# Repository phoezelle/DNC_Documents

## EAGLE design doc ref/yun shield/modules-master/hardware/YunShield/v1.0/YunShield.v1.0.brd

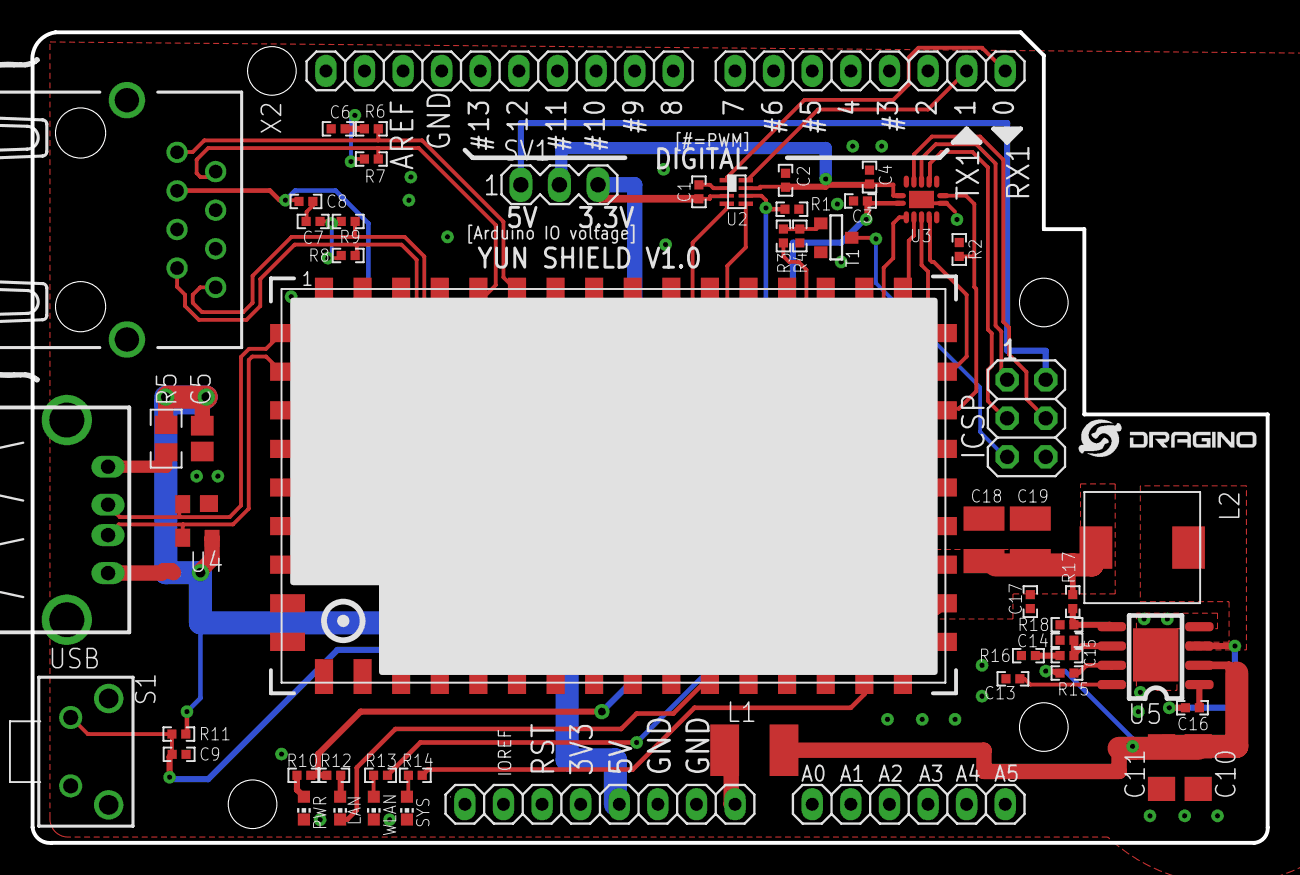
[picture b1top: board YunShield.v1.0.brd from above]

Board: 2 copper layers, 81.3 x 53.3 mm, 58 parts (0 on the bottom side), 48 nets.

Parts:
C1, C2, C3, C4: 0.1uF; C0402
C5: 10uF, 10V; C0805
C6, C7, C8: 0.1u 10v; C0402
C9: 0.1u NL; C0402
C10: 10uF 25V; C1206
C11: 10uF 25v NL; C1206
C13: 0.1u 10V; C0402
C14, C17: NL; C0402
C15: 3900pF 25V; C0402
C16: 0.01uF 16V; C0402
C18, C19: 22uF; C1210
ICSP: ICSP; 2X03
J2, J3: 8x1F-H8.5; 1X08
J4: 6x1F-H8.5; 1X06
JP1: 10x1F-H8.5; 1X10
L1: 500ma; L1812
L2: 10uH; INDUCTOR-74
LAN: Yellow; CHIP-LED0603
PWR: Yellow; CHIP-LED0603
R1, R2: 10k; R0402
R3, R4: 47k; R0402
R5: PTC; R0805
R6, R7, R8, R9: 49.9R; R0402
R10, R12: 330R; R0402
R11, R15: 100K; R0402
R13, R14: 270R; R0402
R16: 6.81K; R0402
R17: 26.1K; R0402
R18: 10K; R0402
S1: SWITCH_6X6X5
SV1: MA03-1
SYS: Yellow; CHIP-LED0603
T1: AP2302GN-HF/SOT23; SOT-23
U1: HE; HE50
U2: NTB0102GT; NXP-SOT833-1
U3: NTB0104; DHVQFN14
U4: YSSR05; SOT143
U5: RT8250; RT8250-SOP8
U$1: LOGO-NEW; LOGO-SILK-NEW
USB: PN87520
WLAN: Yellow; CHIP-LED0603
X2: RJ111BE

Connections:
2.5V: C3.2, U1.36, U3.1
+3V3: C1.2, C17.1, C18.1, C19.1, L2.P$2, R10.1, R12.1, R17.2, SV1.3, U1.23, U1.24, U2.3
+5V: C5.1, ICSP.2, J3.5, R5.1, R11.2, SV1.1, U4.4
/RESET: ICSP.5, T1.1
CTRL_2.0V: C8.1, U1.2, X2.3
GND: C1.1, C2.1, C3.1, C4.1, C5.2, C6.2, C7.2, C8.2, C9.2, C10.1, C11.1, C13.2, C14.2, C17.2, C18.2, C19.2, ICSP.6, J3.6, J3.7, JP1.7, PWR.C, R1.1, R2.1, R4.2, R16.1, R18.1, S1.2, S1.3, S1.4, SYS.C, T1.2, U1.1, U1.4, U1.7, U1.10, U1.13, U1.22, U1.25, U1.26, U1.32, U1.35, U1.40, U1.42, U1.44, U1.45, U1.48, U2.2, U3.7, U3.EXP, U4.1, U5.4, U5.9, USB.4, WLAN.C
GPIO18: U1.18, U3.5
GPIO19: R2.2, U1.19, U3.8
GPIO20: R3.2, U1.20
GPIO21: U1.16, U3.3
GPIO22: U1.17, U3.4
GPIO23: U1.21, U3.2
GPIO24: R1.2, U1.3, U2.6
GPIO28: R14.1, U1.27
JUMPSTART: C9.1, R11.1, S1.1, U1.37
LED_P0: LAN.C, U1.31
LED_WLAN: R13.1, U1.30
MISO: ICSP.1, U3.11
MOSI: ICSP.4, U3.12
unnamed: R3.1, R4.1, T1.3
unnamed: R5.2, USB.1
unnamed: C6.1, R6.1, R7.1
unnamed: PWR.A, R10.2
unnamed: C7.1, R8.1, R9.1
unnamed: LAN.A, R12.2
unnamed: R13.2, WLAN.A
unnamed: R14.2, SYS.A
unnamed: C10.2, C11.2, L1.2, R15.2, U5.2
unnamed: R15.1, U5.7
unnamed: R17.1, R18.2, U5.5
unnamed: C13.1, U5.8
unnamed: C14.1, C15.1, U5.6
unnamed: C15.2, R16.2
unnamed: C16.1, U5.1
unnamed: C16.2, L2.P$1, U5.3
P0_RX_N: R9.2, U1.8, X2.8
P0_RX_P: R8.2, U1.9, X2.7
P0_TX_N: R7.2, U1.5, X2.2
P0_TX_P: R6.2, U1.6, X2.1
RX: J2.1, U2.1
SCK: ICSP.3, U3.10
TX: J2.2, U2.8
UART_RX: U1.33, U2.5
UART_TX: U1.34, U2.4
USB_N: U1.50, U4.2, USB.2
USB_P: U1.49, U4.3, USB.3
VDC: C2.2, C4.2, SV1.2, U2.7, U3.14
VIN: J3.8, L1.1

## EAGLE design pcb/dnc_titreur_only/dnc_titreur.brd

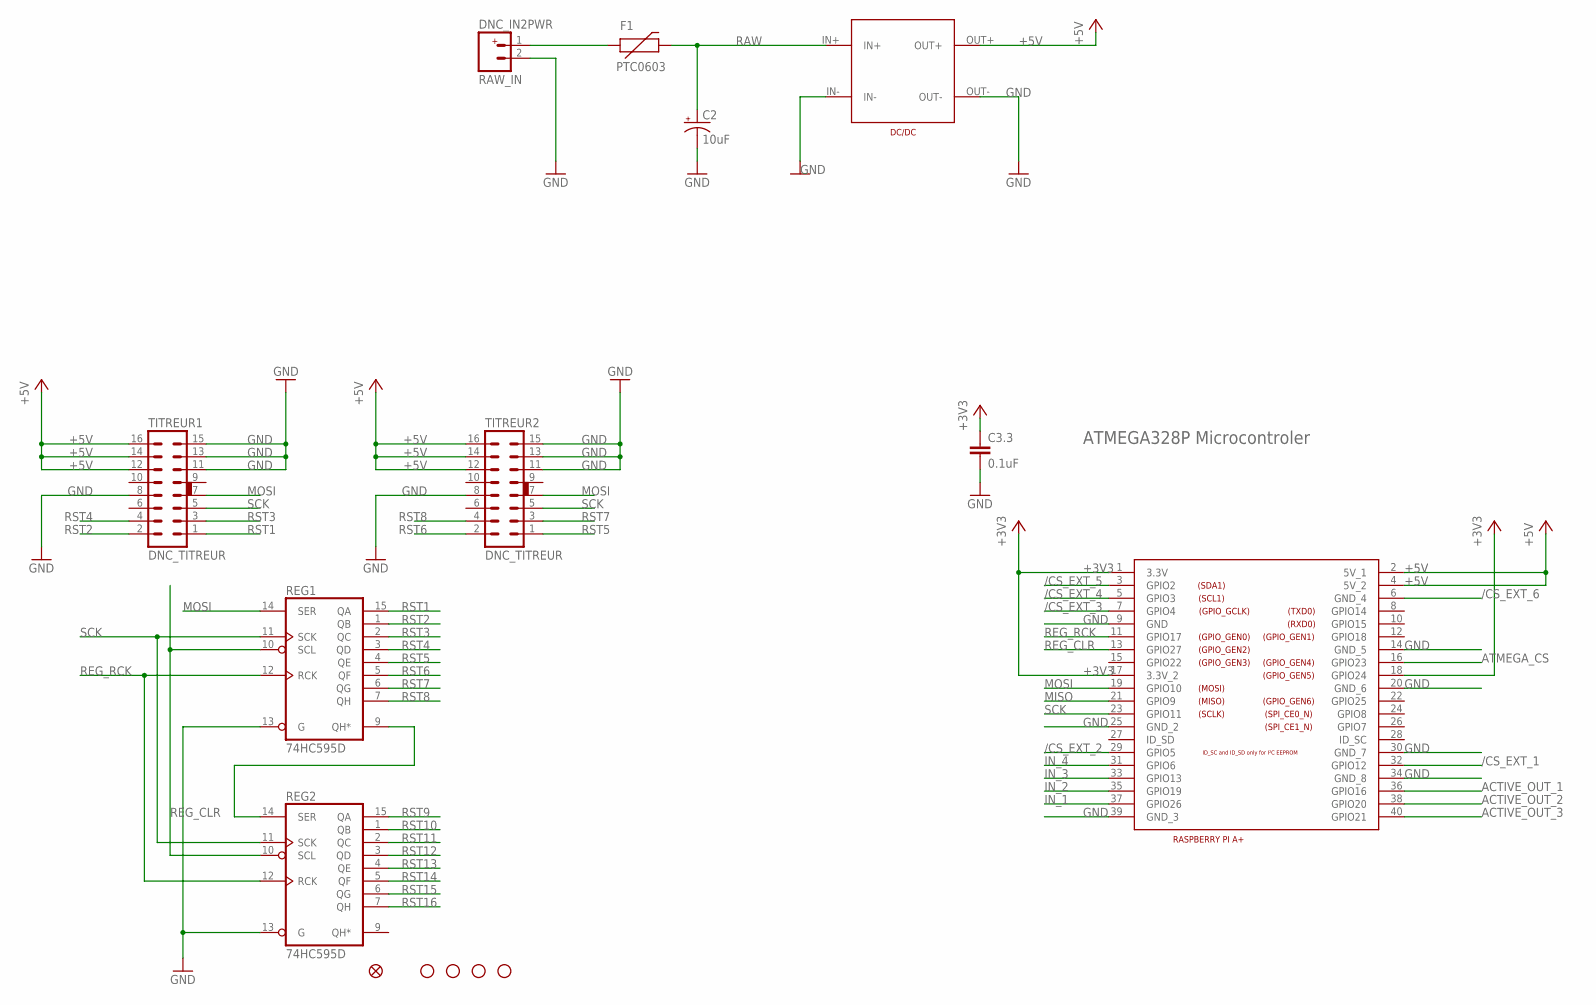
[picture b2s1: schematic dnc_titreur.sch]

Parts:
C2: 10uF; EIA3216
C3.3: 0.1uF; C0805
F1: PTC0603; 0603
JP14: FIDUCIAL1X2.5; FIDUCIAL-1X2.5
JP15, JP16, JP17, JP18: STAND-OFF
RAW_IN: DNC_IN2PWR; DNC_IN2_PWR
REG1, REG2: 74HC595D; SO16
TITREUR1, TITREUR2: DNC_TITREUR
U$4: RASPIA+
U$5: DC/DC_SEED

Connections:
+3V3: C3.3.1, U$4.1 (3.3V), U$4.17 (3.3V_2), U$4.18 (GPIO24)
+5V: TITREUR1.12, TITREUR1.14, TITREUR1.16, TITREUR2.12, TITREUR2.14, TITREUR2.16, U$4.2 (5V_1), U$4.4 (5V_2), U$5.OUT+
/CS_EXT_1: U$4.32 (GPIO12)
/CS_EXT_2: U$4.29 (GPIO5)
/CS_EXT_3: U$4.7 (GPIO4)
/CS_EXT_4: U$4.5 (GPIO3)
/CS_EXT_5: U$4.3 (GPIO2)
/CS_EXT_6: U$4.6 (GND_4)
ACTIVE_OUT_1: U$4.36 (GPIO16)
ACTIVE_OUT_2: U$4.38 (GPIO20)
ACTIVE_OUT_3: U$4.40 (GPIO21)
ATMEGA_CS: U$4.16 (GPIO23)
GND: C2.C (-), C3.3.2, RAW_IN.2, REG1.8 (GND), REG1.13 (G), REG2.8 (GND), REG2.13 (G), TITREUR1.8, TITREUR1.11, TITREUR1.13, TITREUR1.15, TITREUR2.8, TITREUR2.11, TITREUR2.13, TITREUR2.15, U$4.9 (GND), U$4.14 (GND_5), U$4.20 (GND_6), U$4.25 (GND_2), U$4.30 (GND_7), U$4.34 (GND_8), U$4.39 (GND_3), U$5.IN-, U$5.OUT-
IN_1: U$4.37 (GPIO26)
IN_2: U$4.35 (GPIO19)
IN_3: U$4.33 (GPIO13)
IN_4: U$4.31 (GPIO6)
MISO: U$4.21 (GPIO9)
MOSI: REG1.14 (SER), TITREUR1.7, TITREUR2.7, U$4.19 (GPIO10)
unnamed: REG1.9 (QH*), REG2.14 (SER)
unnamed: F1.1, RAW_IN.1
RAW: C2.A (+), F1.2, U$5.IN+
REG_CLR: REG1.10 (SCL), REG2.10 (SCL), U$4.13 (GPIO27)
REG_RCK: REG1.12 (RCK), REG2.12 (RCK), U$4.11 (GPIO17)
RST1: REG1.15 (QA), TITREUR1.1
RST2: REG1.1 (QB), TITREUR1.2
RST3: REG1.2 (QC), TITREUR1.3
RST4: REG1.3 (QD), TITREUR1.4
RST5: REG1.4 (QE), TITREUR2.1
RST6: REG1.5 (QF), TITREUR2.2
RST7: REG1.6 (QG), TITREUR2.3
RST8: REG1.7 (QH), TITREUR2.4
RST9: REG2.15 (QA)
RST10: REG2.1 (QB)
RST11: REG2.2 (QC)
RST12: REG2.3 (QD)
RST13: REG2.4 (QE)
RST14: REG2.5 (QF)
RST15: REG2.6 (QG)
RST16: REG2.7 (QH)
SCK: REG1.11 (SCK), REG2.11 (SCK), TITREUR1.5, TITREUR2.5, U$4.23 (GPIO11)
VCC: REG1.16 (VCC), REG2.16 (VCC)

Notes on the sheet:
ATMEGA328P Microcontroler

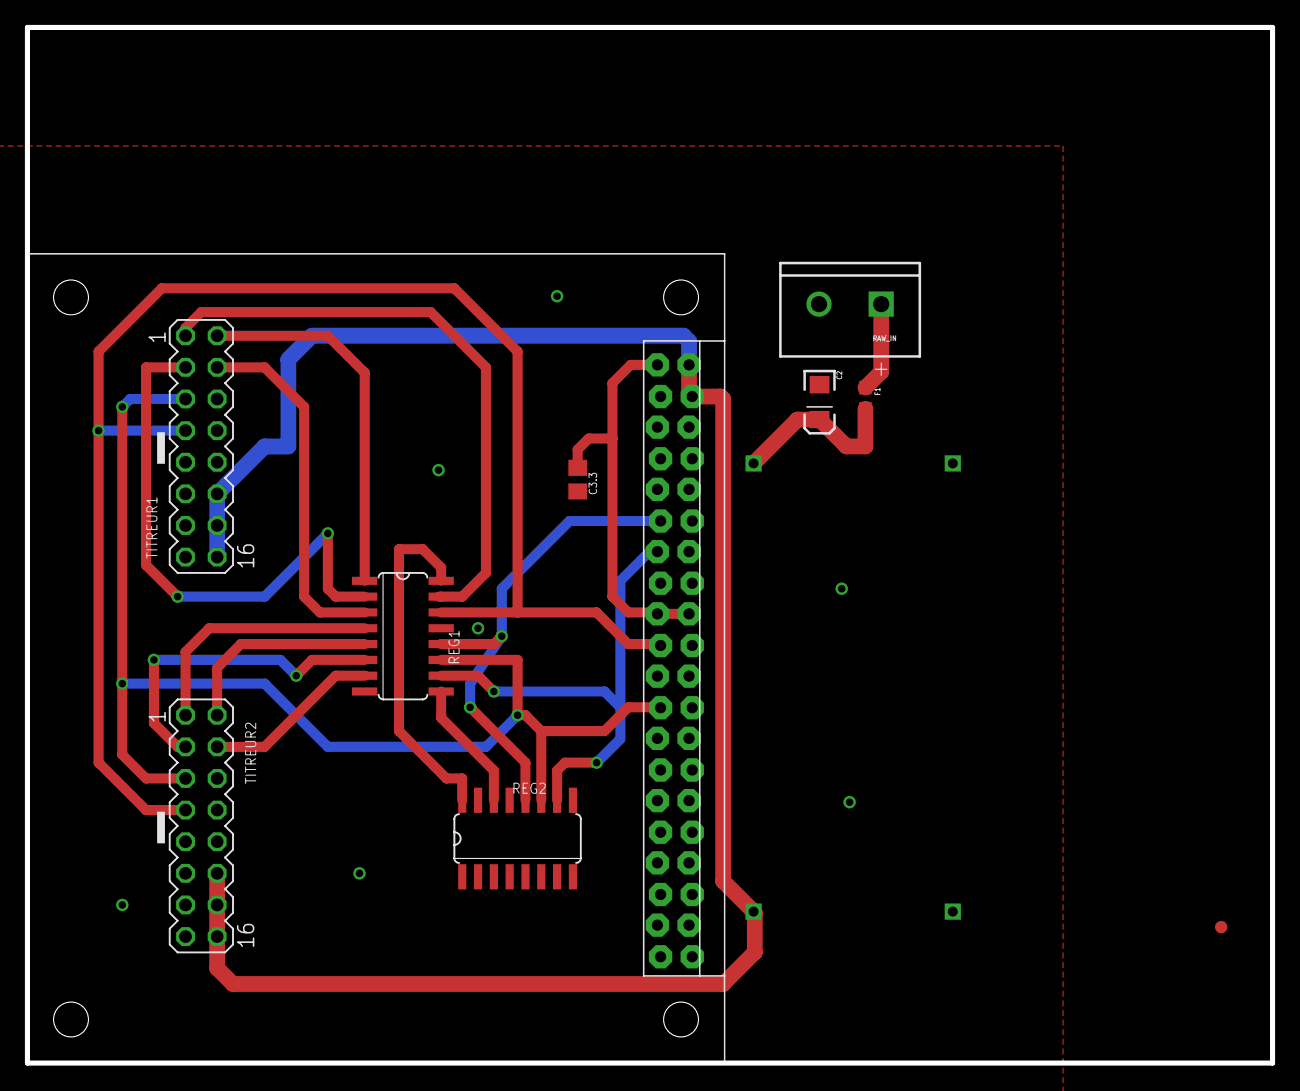
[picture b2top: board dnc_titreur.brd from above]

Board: 2 copper layers, 100.0 x 83.2 mm, 15 parts (0 on the bottom side), 19 nets.

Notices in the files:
parts and their libraries:
SparkFun: Licensing: CC v3.0 Share-Alike You are welcome to use this library for commercial purposes.
SparkFun-PowerIC: Licensing: Creative Commons ShareAlike 4.0 International - https://creativecommons.org/licenses/by-sa/4.0
